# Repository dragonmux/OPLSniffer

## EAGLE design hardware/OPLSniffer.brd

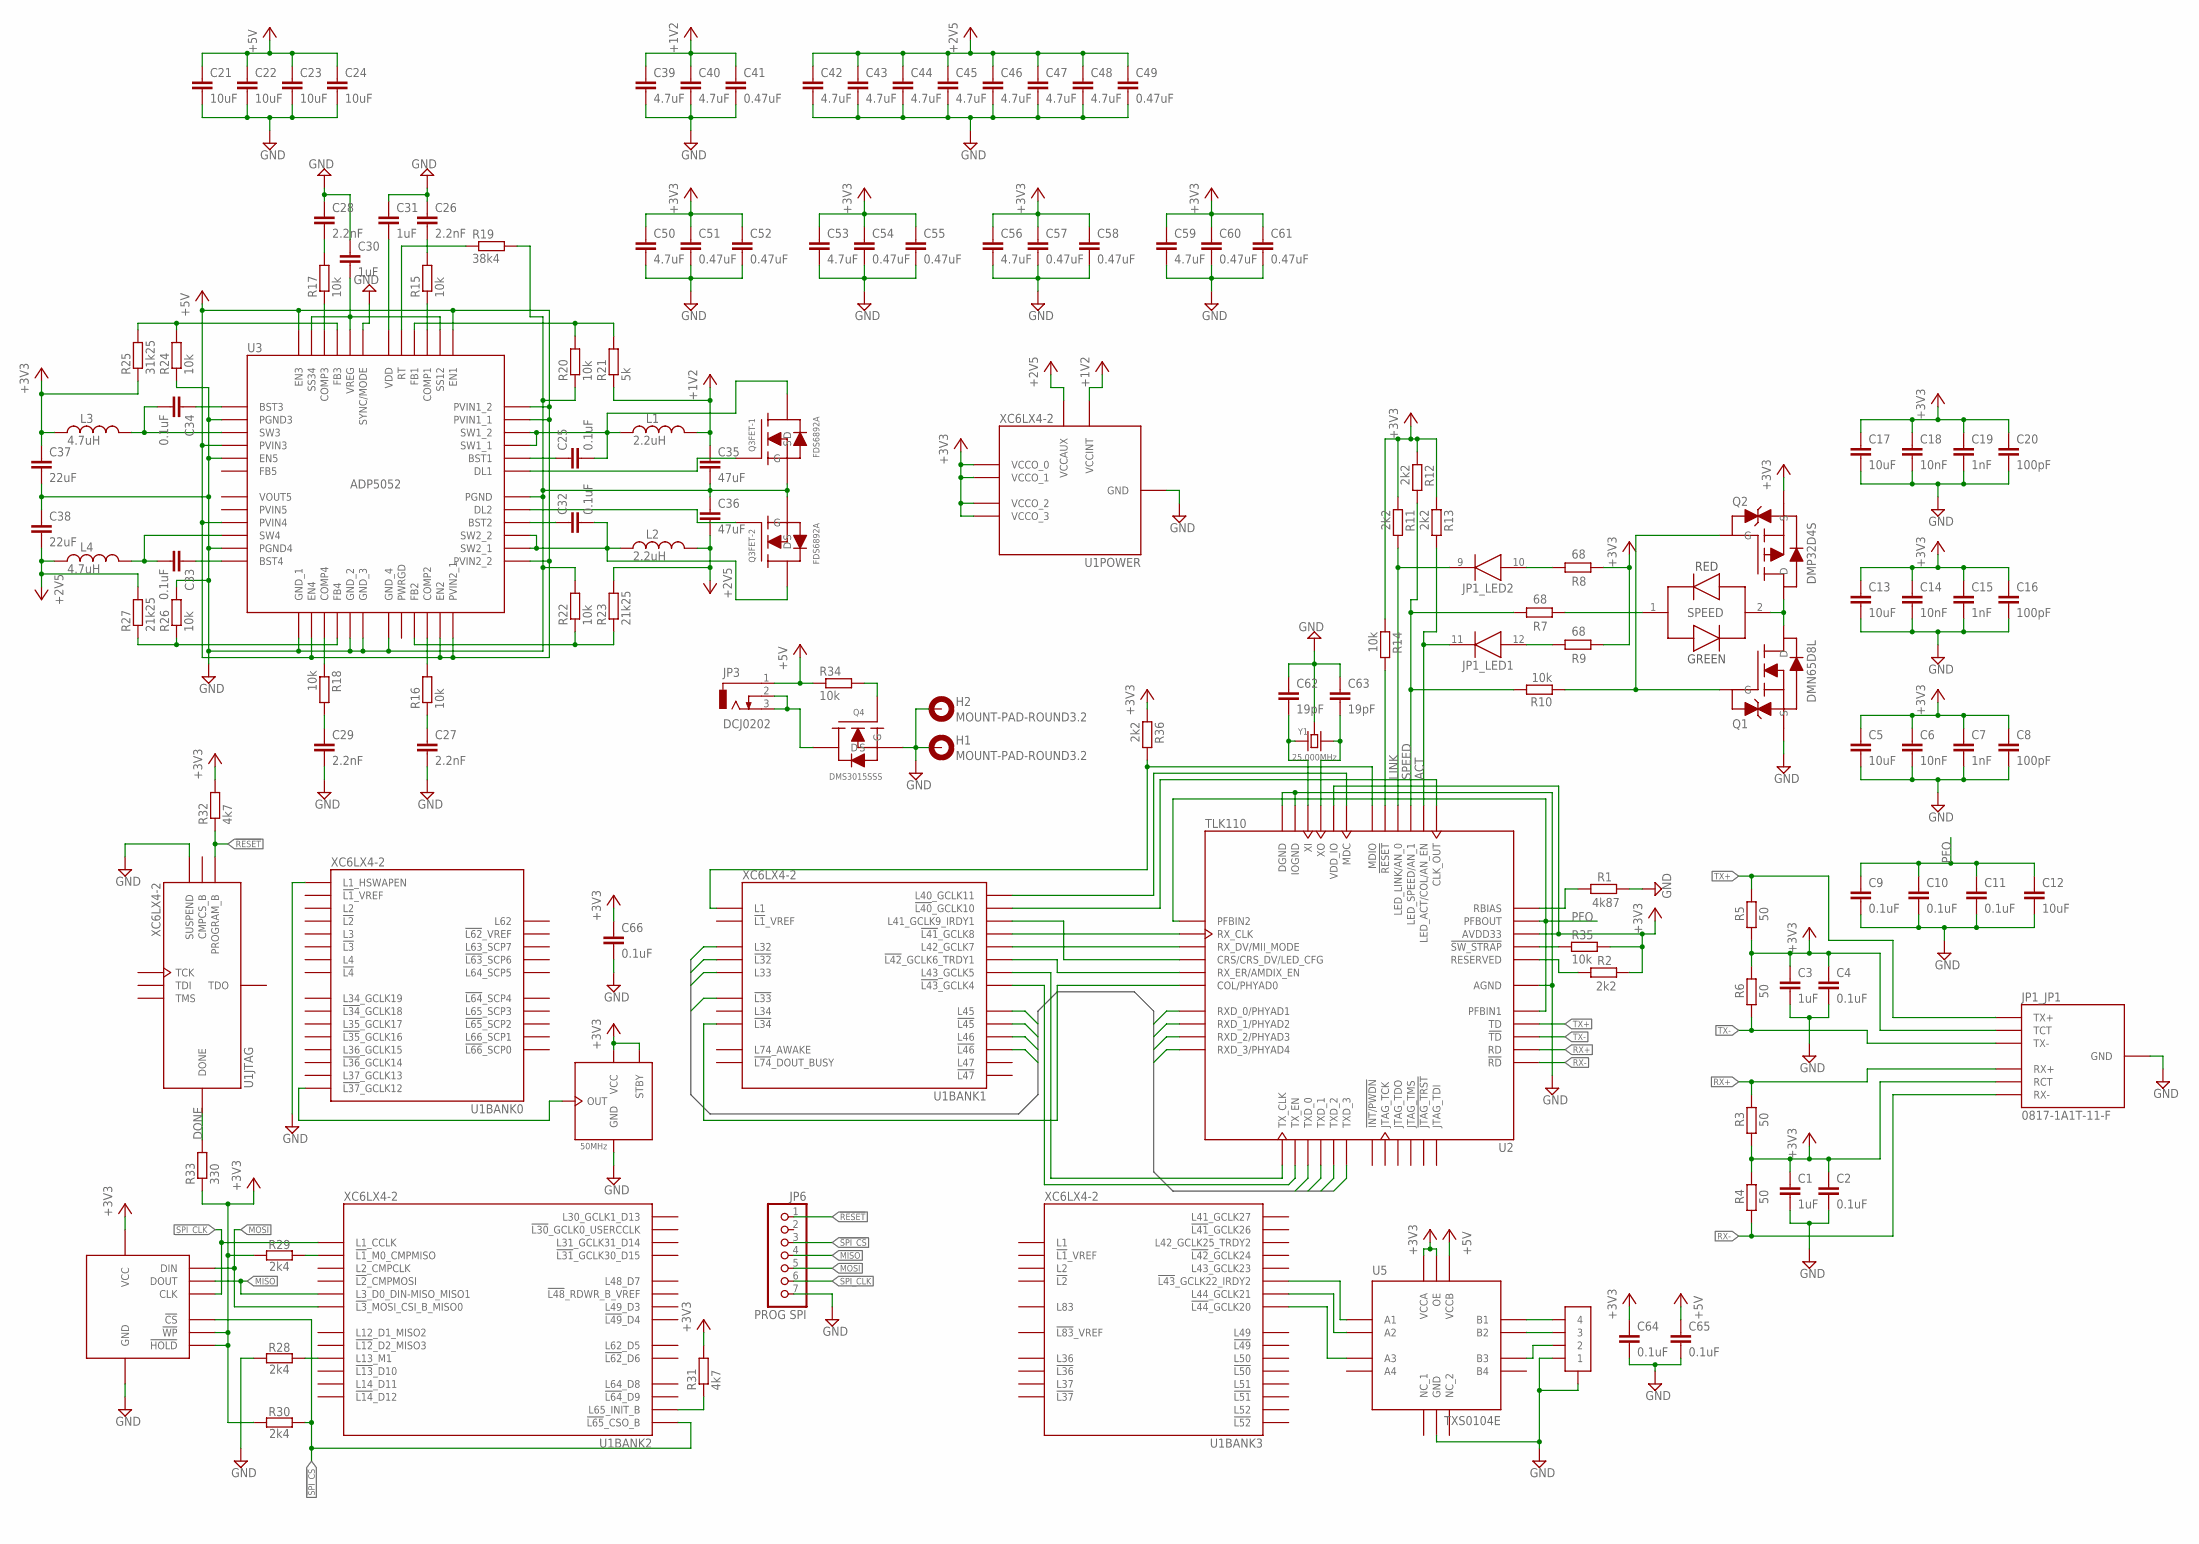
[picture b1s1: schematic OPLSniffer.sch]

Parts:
C1, C3, C30, C31: 1uF; C0603K; MPN MC0603X105M6R3CT
C2, C4, C9, C10, C11, C25, C32, C33, C34, C64, C65, C66: 0.1uF; C0603K; MPN MC0603B104J250CT
C5, C12, C13, C17, C22, C23, C24: 10uF; C0805K; MPN MC0805X106K250CT
C6, C14, C18: 10nF; C0603K; MPN MCCA000238
C7, C15, C19: 1nF; C0603K; MPN MC0603B102K500CT
C8, C16, C20: 100pF; C0603K; MPN MCCA001175
C21: 10uF; C0805K; MPN GRM21BR61E106KA73L
C26, C27, C28, C29: 2.2nF; C0603K; MPN MCCA001160
C35, C36: 47uF; C1206K; MPN GRM31CR60J476KE19L
C37, C38: 22uF; C0805K; MPN C0805C226M9PACTU
C39, C40, C42, C43, C44, C45, C46, C47, C48, C50, C53, C56, C59: 4.7uF; C0603K; MPN MC0603X475K6R3CT
C41, C49, C51, C52, C54, C55, C57, C58, C60, C61: 0.47uF; C0603K; MPN MC0603X474K100CT
C62, C63: 19pF; C0603K; MPN C0603C180J5GACTU
H1, H2: MOUNT-PAD-ROUND3.2; 3,2-PAD
JP1: 0817-1A1T-11-F; MPN 0817-1A1T-11-F
JP3: DCJ0202
JP4: OPL2; 53261-0471_PICOBLADE
JP6: PROG SPI; PINHEAD_1X7
L1, L2: 2.2uH; NRS4018; MPN NRS4018T2R2MDGJ
L3, L4: 4.7uH; NRS4018; MPN NRS4018T4R7MDGJ
OSC1: 50MHz; SMD3225; MPN ASE-50.000MHZ-L-R-T
Q1: DMN65D8L; SOT23
Q2: DMP32D4S; SOT23; MPN DMP32D4S-13
Q3: FDS6892A; SOIC8
Q4: DMS3015SSS; SOIC8
R1: 4k87; R0603; MPN CRCW06034K87FKEA
R2, R11, R12, R13, R36: 2k2; R0603; MPN MCMR06X2201FTL
R3, R4, R5, R6: 50; R0603; MPN CRCW060350R0FKEA
R7, R8, R9: 68; R0603; MPN MCMR06X68R0FTL
R10, R14, R15, R16, R17, R18, R20, R22, R24, R26, R34, R35: 10k; R0603; MPN MC0063W0603110K
R19: 38k4; R0603; MPN CRCW060338K3FKEA
R21: 5k; R0603; MPN MC0063W060314K99
R23, R27: 21k25; R0603; MPN MC0063W0603121K5
R25: 31k25; R0603; MPN CRCW060331K6FKEA
R28, R29, R30: 2k4; R0603; MPN MCMR06X2401FTL
R31, R32: 4k7; R0603; MPN MCMR06X4701FTL
R33: 330; R0603; MPN MCMR06X3300FTL
SPEED: RG-LED; CHIPLED_0805; MPN KPB-2012SURKCGKC
U1: XC6LX4-2; TQFP144
U2: TLK110; LQFP48
U3: ADP5052; LFSCP48
U4: M25P16-VMN6P; SOIC8; MPN M25P16-VMN6P
U5: TXS0104E; TSSOP14
Y1: 25.000MHz; SMD3225; MPN MCSJK-7U-25.00-12-10-60-B-10

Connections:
!RESET: JP6.1, R32.1, U1.37 (PROGRAM_B)
!SPI_CS: JP6.3, R30.2, U1.38 (!L65!_CSO_B), U4.1 (!CS)
+1V2: C35.1, C39.1, C40.1, C41.1, L1.2, R21.1, U1.19 (VCCINT), U1.28 (VCCINT), U1.52 (VCCINT), U1.89 (VCCINT), U1.128 (VCCINT)
+2V5: C36.2, C38.2, C42.1, C43.1, C44.1, C45.1, C46.1, C47.1, C48.1, C49.1, L2.2, L4.1, R23.2, R27.2, U1.20 (VCCAUX), U1.36 (VCCAUX), U1.53 (VCCAUX), U1.90 (VCCAUX), U1.129 (VCCAUX)
+3V3: C1.1, C2.1, C3.1, C4.1, C5.1, C6.1, C7.1, C8.1, C13.1, C14.1, C15.1, C16.1, C17.1, C18.1, C19.1, C20.1, C37.1, C50.1, C51.1, C52.1, C53.1, C54.1, C55.1, C56.1, C57.1, C58.1, C59.1, C60.1, C61.1, C64.1, C66.1, JP1.3 (TCT), JP1.6 (RCT), L3.1, OSC1.1 (STBY), OSC1.4 (VCC), Q2.2 (S), R2.2, R3.1, R4.2, R5.1, R6.2, R8.1, R9.1, R11.1, R12.1, R13.1, R14.1, R25.1, R29.1, R30.1, R31.2, R32.2, R33.1, R35.2, R36.1, U1.4 (VCCO_3), U1.18 (VCCO_3), U1.31 (VCCO_3), U1.42 (VCCO_2), U1.63 (VCCO_2), U1.76 (VCCO_1), U1.86 (VCCO_1), U1.103 (VCCO_1), U1.122 (VCCO_0), U1.125 (VCCO_0), U1.135 (VCCO_0), U2.22 (AVDD33), U2.32 (VDD_IO), U2.48 (VDD_IO), U4.3 (!WP), U4.7 (!HOLD), U4.8 (VCC), U5.1 (VCCA), U5.8 (OE)
+5V: C21.1, C22.1, C23.1, C24.1, C65.1, JP3.1, R34.1, U3.4 (PVIN3), U3.9 (PVIN4), U3.14 (EN4), U3.23 (EN2), U3.24 (PVIN2_1), U3.25 (PVIN2_2), U3.35 (PVIN1_1), U3.36 (PVIN1_2), U3.37 (EN1), U3.48 (EN3), U5.14 (VCCB)
ACT: JP1.11 (C), R13.2, U2.26 (LED_ACT/COL/AN_EN)
DONE: R33.2, U1.71 (DONE)
GND: C1.2, C2.2, C3.2, C4.2, C5.2, C6.2, C7.2, C8.2, C9.2, C10.2, C11.2, C12.2, C13.2, C14.2, C15.2, C16.2, C17.2, C18.2, C19.2, C20.2, C21.2, C22.2, C23.2, C24.2, C26.1, C27.2, C28.1, C29.2, C30.1, C31.1, C35.2, C36.1, C37.2, C38.1, C39.2, C40.2, C41.2, C42.2, C43.2, C44.2, C45.2, C46.2, C47.2, C48.2, C49.2, C50.2, C51.2, C52.2, C53.2, C54.2, C55.2, C56.2, C57.2, C58.2, C59.2, C60.2, C61.2, C62.1, C63.1, C64.2, C65.2, C66.2, H1.B3,2, H2.B3,2, JP1.4 (GND), JP1.5 (GND), JP1.GND1 (GND), JP1.GND2 (GND), JP4.1, JP4.GND1 (GND), JP4.GND2 (GND), JP6.7, OSC1.2 (GND), Q1.2 (S), Q3.1 (S), Q3.3 (S), Q4.1 (S), Q4.2 (S), Q4.3 (S), R1.2, R19.2, R20.1, R22.2, R24.1, R26.2, R28.1, U1.3 (GND), U1.13 (GND), U1.25 (GND), U1.49 (GND), U1.54 (GND), U1.68 (GND), U1.73 (SUSPEND), U1.77 (GND), U1.91 (GND), U1.96 (GND), U1.108 (GND), U1.113 (GND), U1.130 (GND), U1.136 (GND), U1.144 (L1_HSWAPEN), U2.15 (AGND), U2.19 (AGND), U2.35 (IOGND), U2.36 (DGND), U2.47 (IOGND), U3.2 (PGND3), U3.5 (EN5), U3.11 (PGND4), U3.13 (GND_1), U3.17 (GND_2), U3.18 (GND_3), U3.19 (GND_4), U3.30 (PGND), U3.43 (SYNC/MODE), U3.PAD (PGND), U4.4 (GND), U5.7 (GND), Y1.2 (GND), Y1.4 (GND)
LINK: JP1.9 (C), R11.2, U2.28 (LED_LINK/AN_0)
MISO: JP6.4, U1.65 (L3_D0_DIN-MISO_MISO1), U4.2 (DOUT)
MOSI: JP6.5, U1.64 (!L3!_MOSI_CSI_B_MISO0), U4.5 (DIN)
unnamed: R1.1, U2.24 (RBIAS)
unnamed: R2.1, U2.20 (RESERVED)
unnamed: JP1.12 (A), R9.2
unnamed: R14.2, U2.29 (!RESET)
unnamed: JP1.10 (A), R8.2
unnamed: R7.1, SPEED.1
unnamed: Q1.3 (D), Q2.3 (D), SPEED.2
unnamed: Q1.1 (G), Q2.1 (G), R10.1
unnamed: U1.85 (L43_GCLK5), U2.1 (TX_CLK)
unnamed: C62.2, U2.34 (XI), Y1.1
unnamed: U1.84 (!L43!_GCLK4), U2.2 (TX_EN)
unnamed: U1.87 (!L42!_GCLK6_TRDY1), U2.41 (RX_ER/AMDIX_EN)
unnamed: U1.88 (L42_GCLK7), U2.39 (RX_DV/MII_MODE)
unnamed: U1.92 (!L41!_GCLK8), U2.38 (RX_CLK)
unnamed: U1.94 (!L40!_GCLK10), U2.25 (CLK_OUT)
unnamed: U1.95 (L40_GCLK11), U2.31 (MDC)
unnamed: R36.2, U1.105 (L1), U2.30 (MDIO)
unnamed: OSC1.3 (OUT), U1.123 (!L37!_GCLK12)
unnamed: C32.2, L2.1, Q3.7 (D), Q3.8 (D), U3.26 (SW2_1), U3.27 (SW2_2)
unnamed: C28.2, R17.2
unnamed: R18.1, U3.15 (COMP4)
unnamed: R16.2, U3.22 (COMP2)
unnamed: R15.1, U3.39 (COMP1)
unnamed: R17.1, U3.46 (COMP3)
unnamed: C26.2, R15.2
unnamed: C25.2, L1.1, Q3.5 (D), Q3.6 (D), U3.33 (SW1_1), U3.34 (SW1_2)
unnamed: C29.1, R18.2
unnamed: C27.1, R16.1
unnamed: C30.2, U3.38 (SS12), U3.44 (VREG), U3.47 (SS34)
unnamed: C31.2, U3.42 (VDD)
unnamed: C25.1, U3.32 (BST1)
unnamed: C32.1, U3.28 (BST2)
unnamed: R20.2, R21.2, U3.40 (FB1)
unnamed: C34.1, U3.1 (BST3)
unnamed: C34.2, L3.2, U3.3 (SW3)
unnamed: C33.1, U3.12 (BST4)
unnamed: C33.2, L4.2, U3.10 (SW4)
unnamed: R19.1, U3.41 (RT)
unnamed: JP3.2, JP3.3, Q4.5 (D), Q4.6 (D), Q4.7 (D), Q4.8 (D)
unnamed: R28.2, U1.60 (L13_M1)
unnamed: Q3.2 (G), U3.29 (DL2)
unnamed: Q3.4 (G), U3.31 (DL1)
unnamed: R22.1, R23.1, U3.21 (FB2)
unnamed: R24.2, R25.2, U3.45 (FB3)
unnamed: R26.1, R27.1, U3.16 (FB4)
unnamed: R29.2, U1.69 (!L1!_M0_CMPMISO)
unnamed: R31.1, U1.39 (L65_INIT_B)
unnamed: C63.2, U2.33 (XO), Y1.3 (2)
unnamed: Q4.4 (G), R34.2
unnamed: JP4.2, U5.11 (B3)
unnamed: JP4.3, U5.12 (B2)
unnamed: JP4.4, U5.13 (B1)
unnamed: U1.16 (!L43!_GCLK22_IRDY2), U5.2 (A1)
unnamed: U1.15 (L44_GCLK21), U5.3 (A2)
unnamed: U1.14 (!L44!_GCLK20), U5.4 (A3)
unnamed: U1.93 (L41_GCLK9_IRDY1), U2.40 (CRS/CRS_DV/LED_CFG)
unnamed: U1.97 (!L34), U2.42 (COL/PHYAD0)
unnamed: R35.1, U2.21 (!SW_STRAP)
PFO: C9.1, C10.1, C11.1, C12.1, U2.18 (PFBIN1), U2.23 (PFBOUT), U2.37 (PFBIN2)
PVIN5: U3.8 (PVIN5)
RX+: JP1.7 (RX+), R3.2, U2.14 (RD)
RX-: JP1.8 (RX-), R4.1, U2.13 (!RD)
RXD0: U1.102 (L32), U2.43 (RXD_0/PHYAD1)
RXD1: U1.101 (!L32), U2.44 (RXD_1/PHYAD2)
RXD2: U1.100 (L33), U2.45 (RXD_2/PHYAD3)
RXD3: U1.99 (!L33), U2.46 (RXD_3/PHYAD4)
SPEED: R7.2, R10.2, R12.2, U2.27 (LED_SPEED/AN_1)
SPI_CLK: JP6.6, U1.70 (L1_CCLK), U4.6 (CLK)
TX+: JP1.1 (TX+), R5.2, U2.17 (TD)
TX-: JP1.2 (TX-), R6.1, U2.16 (!TD)
TXD0: U1.83 (L45), U2.3 (TXD_0)
TXD1: U1.82 (!L45), U2.4 (TXD_1)
TXD2: U1.81 (L46), U2.5 (TXD_2)
TXD3: U1.80 (!L46), U2.6 (TXD_3)
VOUT5: U3.7 (VOUT5)

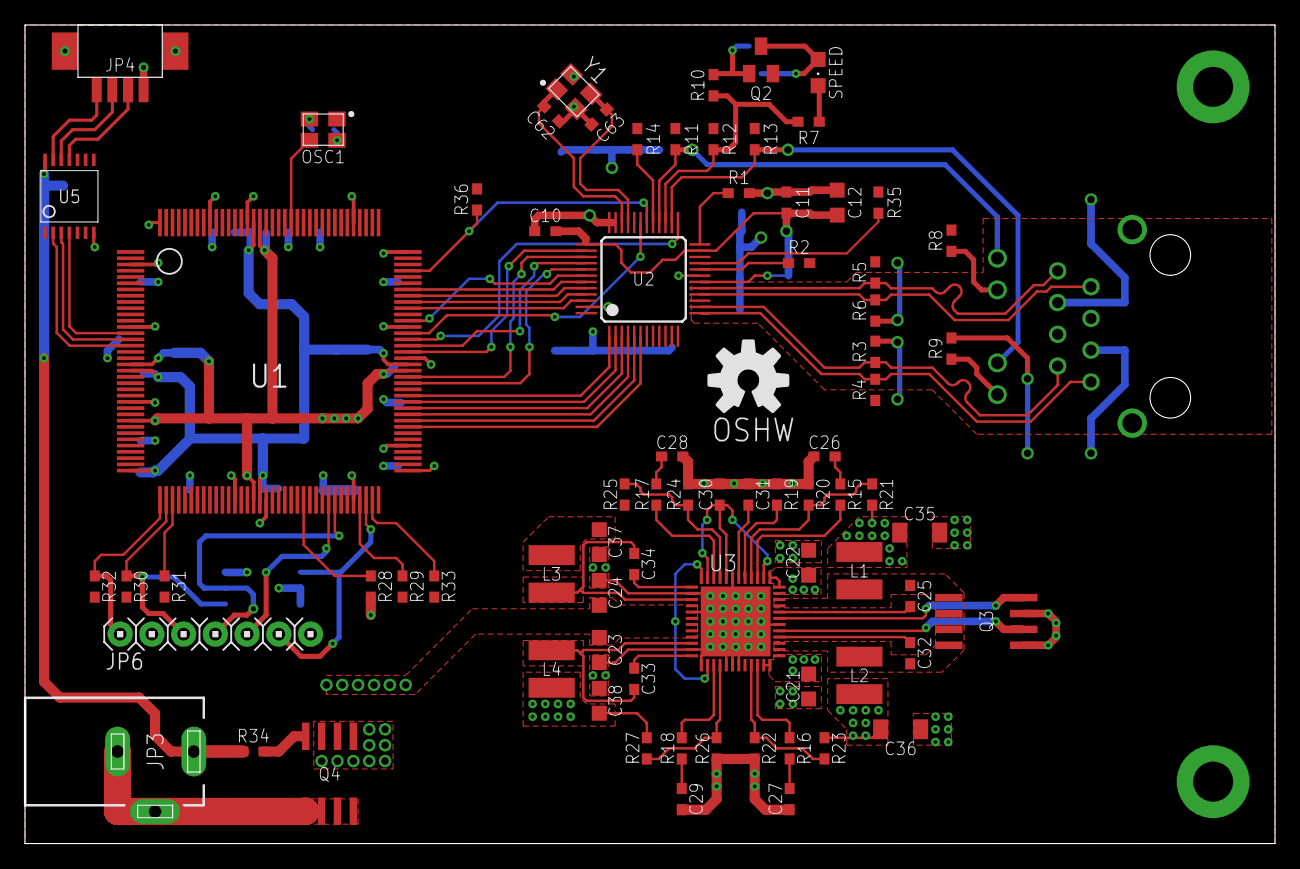
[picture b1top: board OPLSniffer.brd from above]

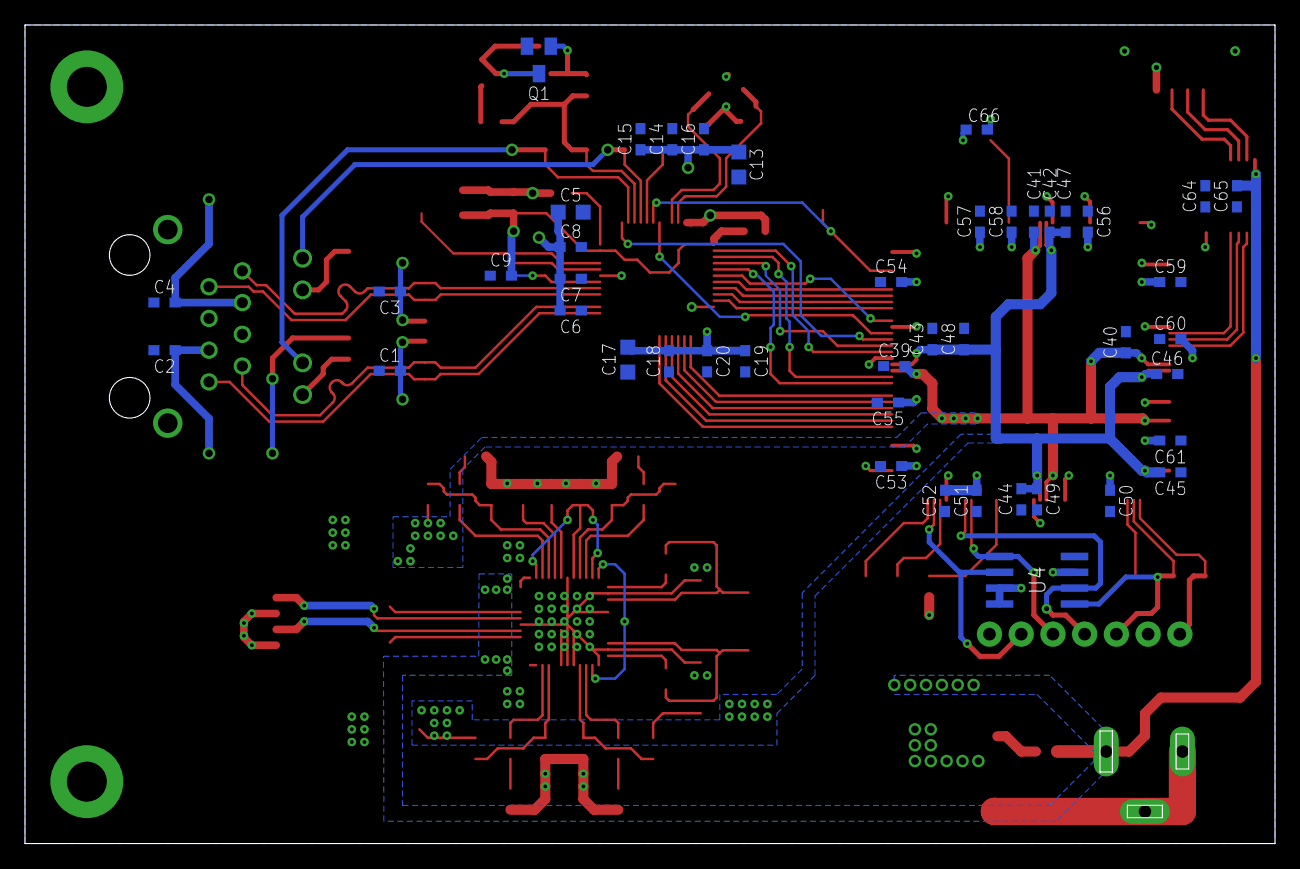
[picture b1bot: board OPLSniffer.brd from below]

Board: 2 copper layers, 100.1 x 65.5 mm, 124 parts (45 on the bottom side), 85 nets.

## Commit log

2021-01-29 Begun implementing a nMigen-based platform/SoC for the OPLSniffer board
2021-01-29 Begun implementing the sniffer hardware for pulling values from the OPL
2021-01-29 Begun implemeting the root hardware module for the SoC
2021-01-29 Implemented the build system for the nMigen gateware to create bitstreams
2021-01-29 Improved the Sniffer interface to allow it to be neatly shimmed for simulation and testing
2021-01-29 Implemented latch recovery from the OPL2 load signal and piped the result into the FIFO
2021-01-29 Created a test for the Sniffer module
2021-01-30 Fixed the signal naming for the input signals from the OPL
2021-01-30 Defined GPIO resources for the platform
2021-01-30 Fleshed out the interface for Sniffer some more, hooking various signals up to the sample BRAM
2021-01-30 Hooked up a couple of signals to the GPIOs to stop the design being completely optimised out
2021-01-30 Improved the simulation of the OPL and the core Sniffer hardware
2021-01-30 Fixed a Vivado-templates-breaking specification for pull-up on the reset signal
2021-01-30 Simplify the test bench for Sniffer with the advice of @the6p4c
2021-01-30 Defined opcodes for the PIC16
2021-01-30 Defined the 50MHz clock the current design has available
2021-01-30 Begun implementing support for peripherals on a bus to build this into a SoC
2021-01-30 Implemented instruction decoding for a PIC16
2021-01-30 Implemented an ALU for the PIC16
2021-01-30 Begun implementing the top-level of the PIC16
2021-01-30 Begun fleshing out a bus interface for the OPL2Sniffer peripheral
2021-01-30 Plugged the PIC16 softcore into the design
2021-01-30 Added a sanity ignore for the build output of the SoC
2021-01-31 Implemented a simple ROM to hook into the PIC16 for an instruction space
2021-01-31 Bonded out the processor peripheral data bits to pins to prevent the tools from optimising it out entirely
2021-01-31 Bonded the ROM to the processor to prevent the tools from optimising the processor out
2021-01-31 Continued fleshing the processor out
2021-01-31 Fixed a small bug in the Sniffer testbench
2021-01-31 Improved the ALU to include a carry/overflow signal
2021-01-31 Created a comprehensive testbench for the PIC16 ALU
2021-01-31 Fixed the durations of the simulation clocks as they were an order of magnitude off (us instead of ns)
2021-01-31 Implemented a series of recognisers for various load/store conditions the PIC16 encounters
2021-01-31 Fixed the naming of the mapALUOpcode result signal
2021-01-31 Fleshed out the PIC16 core more and started to make it behave like the datasheet describes
2021-01-31 Begun the process of simulating and testing the PIC16 softcore
2021-01-31 Cleaned up the naming of two of the load condition functions in the PIC16 core
2021-01-31 Switched the PIC16 instruction decoder to be comb rather than sync
2021-01-31 Added an enable for the PIC16 ALU so it operates in the proper cycle
2021-01-31 Reworked the innards of the PIC16 core and its timings so it maybe starts to function as a PIC16 core
2021-01-31 Begun adding some behaviour asserts to the processor testbench
2021-01-31 Added ignores for sim output
2021-01-31 Cleaned up the ALU slightly and implemented a bit manipulation handling module for the PIC16
2021-01-31 Fixed a breakage in the ALU testbench
2021-01-31 Fixed an ISE warning about not having configured the write port for the ROM properly
2021-01-31 Implemented support for capturing the state of carry from the ALU
2021-01-31 Implemented bit manipulation into the PIC16 core
2021-01-31 Fixed an issue with the calculation of the storesWReg condition signal
2021-01-31 fleshed out some more full cycle runs of the PIC core for its testbench
2021-02-01 Implemented support for bit set/clear
2021-02-01 Implemented support for the BCF/BSF instructions in the PIC16 core
2021-02-01 Fixed a bug in the storesFReg signal generation logic
2021-02-01 Added some testing for the BSF PIC16 instruction
2021-02-26 Implemented the PIC16 8-level call stack
2021-02-26 Fixed a small bug in the PIC16 bit manipulation handling
2021-02-27 Fleshed out the call stack sim some more
2021-02-27 Added testing for the call/return implementation to the processor sim
2021-03-06 Added the Eagle version of the board to the repo for completeness
2021-07-17 Seperated out the read and write halfs of the PIC p-bus to solve a multiple drivers conflict
2021-07-17 Implemented a test bed for iCEBreaker Bitsy to allow easier test and dev of the PIC core
2021-07-19 Added support to the ROM elaboratable for delayed contents filling
2021-07-19 Removed the now extraneous definition of ROM for the Bitsy test target
2021-07-19 Sim rigged the Bitsy code
2021-07-19 Fixed the processor sim to handle the new peripheral bus naming scheme
2021-07-19 Fixed the sim-ability of the Bitsty IOWO elaboratable
2021-07-19 Correct the cycle timings for the peripherals in IOWO
2021-07-19 Fixed the cycle timings of the pRead/pAddr signals in the PIC core
2021-07-19 Implemented the missing data transport for the MOVWF instruction
2021-07-19 Begun implementing the INCSZ/DECSZ instructions
2021-07-19 Completed an implementation of DECFSZ/INCFSZ
2021-07-19 Introduced CPU pause states and advanced the i-bus timings so the processor works with the available ROM implementation
2021-07-19 Implemented the zero flag register field
2021-07-19 Implemented reset elongation for the processor so it can set its first cycle up correctly
2021-07-19 Fixed the gpioB.oe assignment as the signal is one bit wide
2021-07-19 Advanced the reset timings in the real gateware same as the test Bitsy gateware
2021-07-19 Added the sim for the Bitsy warmboot elaboratable
2021-07-19 Added the sim for the Bitsy hardware that shows the processor works and the peripherals are properly timed
2021-07-19 Fixed the imports in the Bitsy test gateware
2021-07-19 Implemented a proper instruction bus record type for the processor
2021-07-19 Switched the real gateware to using the new iBus
2021-07-21 Begun implementing a bus elaborable for the peripheral bus
2021-07-21 Added some missing __init__.py's
2021-07-21 Switched the PIC core over to using the new pBus system
2021-07-21 Fixed up the main OPLSniffer gateware
2021-07-21 Added a code of conduct and licensing
2021-07-22 Moved the rest of the test SoC over to PICBus and implemented a GPIO primitive
2021-07-22 Bug fixing for the PICBus implementation
2021-07-22 Updated the code for the PIC to reflect the peripherals changes
2021-07-22 Added a PMOD connector as a second GPIO to the test Bitsy gateware
2021-07-22 Added some critical path optimisations to the ALU and pause logic
2021-07-22 Begun folding execution of the sims into the CLI
2021-07-22 Moved the call stack sim over to the new sim runner
2021-07-22 Fixed up the processor sim and integrated it into the new sim runner
2021-09-17 Completed some significant re-timing on the PIC core to increase its f(max)
2021-09-17 Added a type annotation to the RAM block in the Bitsy test gateware
2021-09-17 Split the ALU into an arithmetic and a logic unit to help timings on the UP5K
2021-09-17 Cleaned up the bit manip unit with Signal.bit_select()
2021-09-17 Timing improvement from makign the store bits sync
2021-09-18 More retiming goodness
2021-09-18 Cleanup and fixes for the processor's opcode types
2021-09-18 More retiming fixes, up to 45.94MHz now
2021-09-18 Fixed the ALU sim
2021-12-21 Switched nmigen -> amaranth as the upstream project has been renamed
2021-12-21 Switched our platform base to the XilinxPlatform per the deprecation warnings
2021-12-21 Cleanup in the ALU sim
2021-12-21 Completed a couple of small improvements to the PIC core
2021-12-21 Updated the SoC bus system to work with amaranth_soc
